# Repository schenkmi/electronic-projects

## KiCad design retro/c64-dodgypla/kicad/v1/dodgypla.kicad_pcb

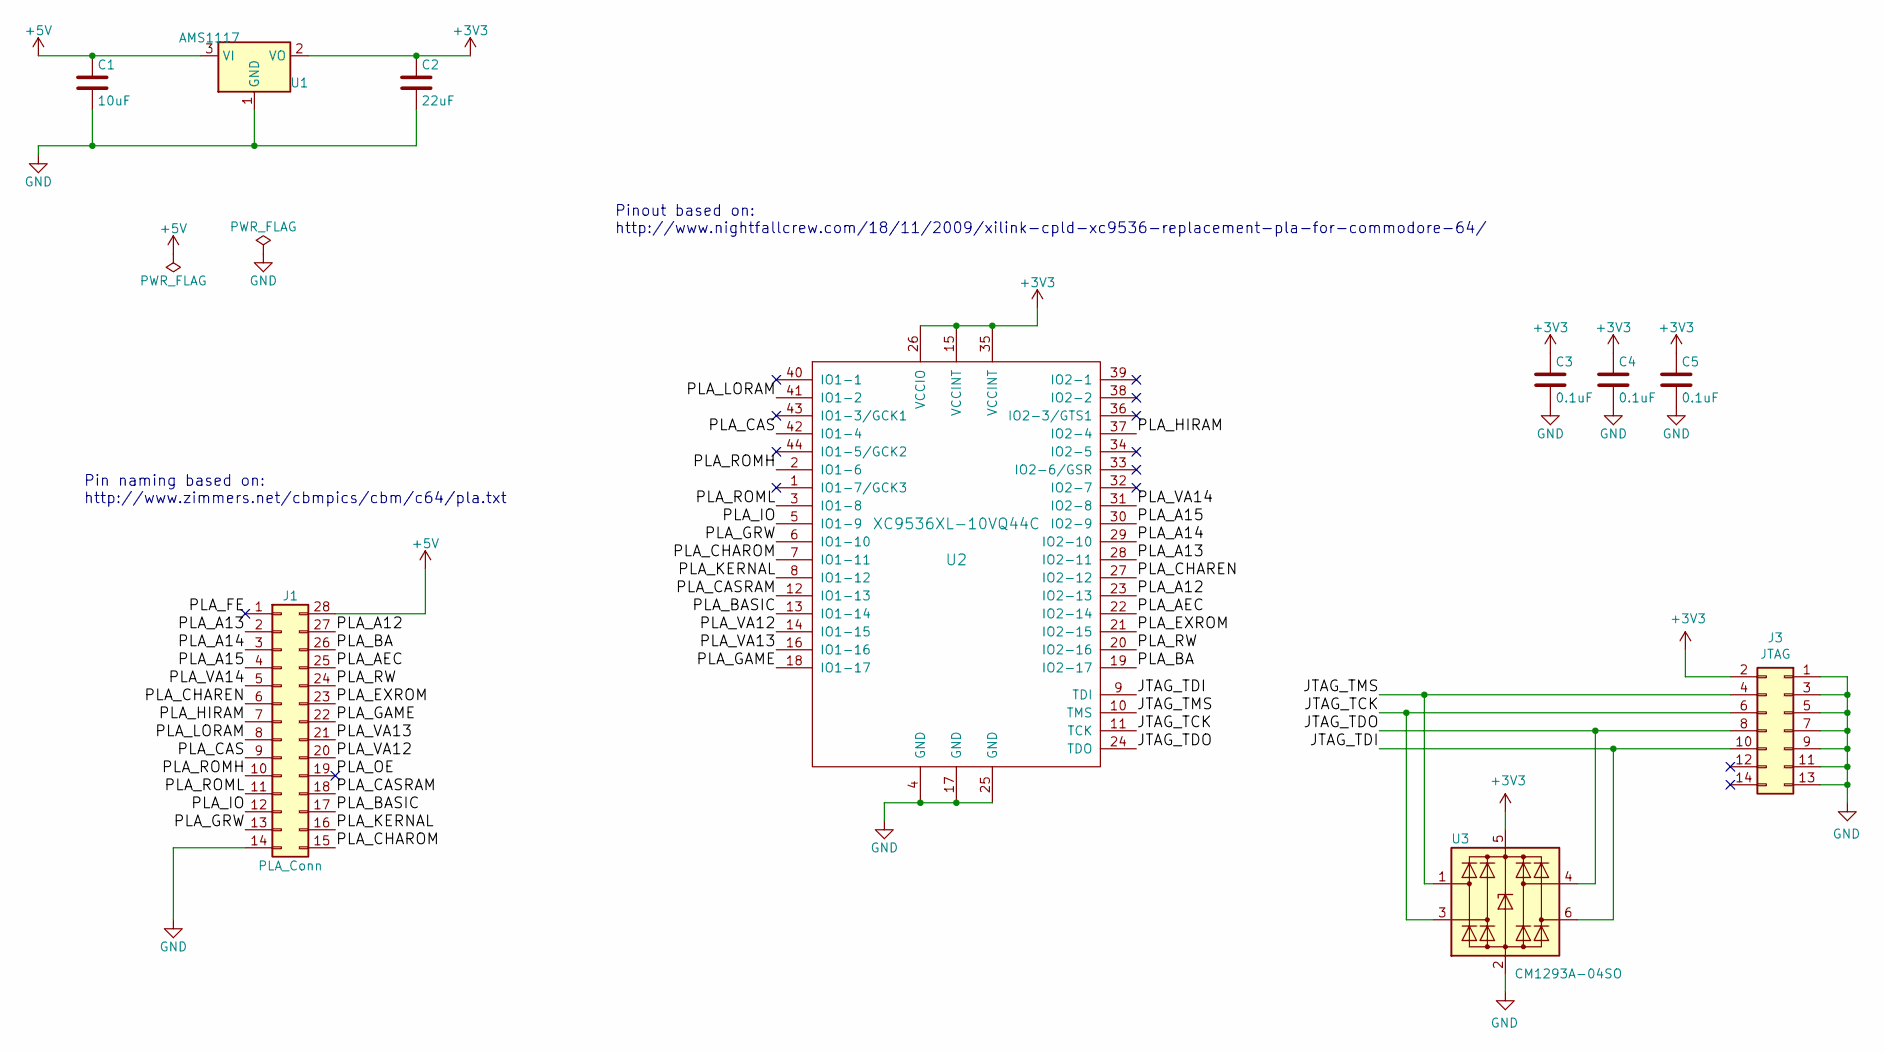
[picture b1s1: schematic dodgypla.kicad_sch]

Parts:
C1: 10uF; C_0805_2012Metric_Pad1.18x1.45mm_HandSolder
C2: 22uF; C_0805_2012Metric_Pad1.18x1.45mm_HandSolder
C3, C4, C5: 0.1uF; C_0805_2012Metric_Pad1.18x1.45mm_HandSolder
J1: PLA_Conn; DIP-28_W15.24mm_Socket
J3: JTAG; PinHeader_2x07_P2.00mm_Vertical
U1: AMS1117; SOT-223-3_TabPin2
U2: XC9536XL-10VQ44C; LQFP-44_10x10mm_P0.8mm
U3: CM1293A−04SO; SC-74-6_1.55x2.9mm_P0.95mm

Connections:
+3V3: C2.1, C3.1, C4.1, C5.1, J3.2, U1.2 (VO), U2.15 (VCCINT), U2.26 (VCCIO), U2.35 (VCCINT), U3.5 (VBUS)
+5V: C1.1, J1.28, U1.3 (VI)
/JTAG_TCK: J3.6, U2.11 (TCK), U3.3 (I/O2)
/JTAG_TDI: J3.10, U2.9 (TDI), U3.6 (I/O4)
/JTAG_TDO: J3.8, U2.24 (TDO), U3.4 (I/O3)
/JTAG_TMS: J3.4, U2.10 (TMS), U3.1 (I/O1)
/PLA_A12: J1.27, U2.23 (IO2-13)
/PLA_A13: J1.2, U2.28 (IO2-11)
/PLA_A14: J1.3, U2.29 (IO2-10)
/PLA_A15: J1.4, U2.30 (IO2-9)
/PLA_AEC: J1.25, U2.22 (IO2-14)
/PLA_BA: J1.26, U2.19 (IO2-17)
/PLA_BASIC: J1.17, U2.13 (IO1-14)
/PLA_CAS: J1.9, U2.42 (IO1-4)
/PLA_CASRAM: J1.18, U2.12 (IO1-13)
/PLA_CHAREN: J1.6, U2.27 (IO2-12)
/PLA_CHAROM: J1.15, U2.7 (IO1-11)
/PLA_EXROM: J1.23, U2.21 (IO2-15)
/PLA_FE: J1.1
/PLA_GAME: J1.22, U2.18 (IO1-17)
/PLA_GRW: J1.13, U2.6 (IO1-10)
/PLA_HIRAM: J1.7, U2.37 (IO2-4)
/PLA_IO: J1.12, U2.5 (IO1-9)
/PLA_KERNAL: J1.16, U2.8 (IO1-12)
/PLA_LORAM: J1.8, U2.41 (IO1-2)
/PLA_OE: J1.19
/PLA_ROMH: J1.10, U2.2 (IO1-6)
/PLA_ROML: J1.11, U2.3 (IO1-8)
/PLA_RW: J1.24, U2.20 (IO2-16)
/PLA_VA12: J1.20, U2.14 (IO1-15)
/PLA_VA13: J1.21, U2.16 (IO1-16)
/PLA_VA14: J1.5, U2.31 (IO2-8)
GND: C1.2, C2.2, C3.2, C4.2, C5.2, J1.14, J3.1, J3.3, J3.5, J3.7, J3.9, J3.11, J3.13, U1.1 (GND), U2.4 (GND), U2.17 (GND), U2.25 (GND), U3.2 (GND)

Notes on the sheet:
Pin naming based on: http://www.zimmers.net/cbmpics/cbm/c64/pla.txt
Pinout based on: http://www.nightfallcrew.com/18/11/2009/xilink-cpld-xc9536-replacement-pla-for-commodore-64/

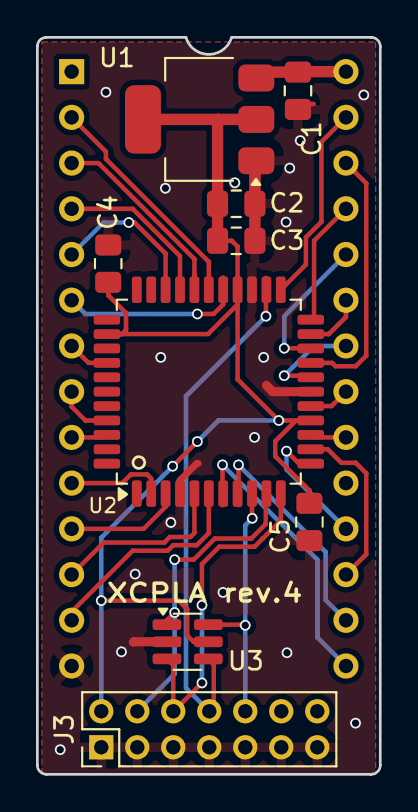
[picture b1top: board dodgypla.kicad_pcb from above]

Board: 2 copper layers, 19.0 x 40.9 mm, 10 parts (0 on the bottom side), 31 nets.

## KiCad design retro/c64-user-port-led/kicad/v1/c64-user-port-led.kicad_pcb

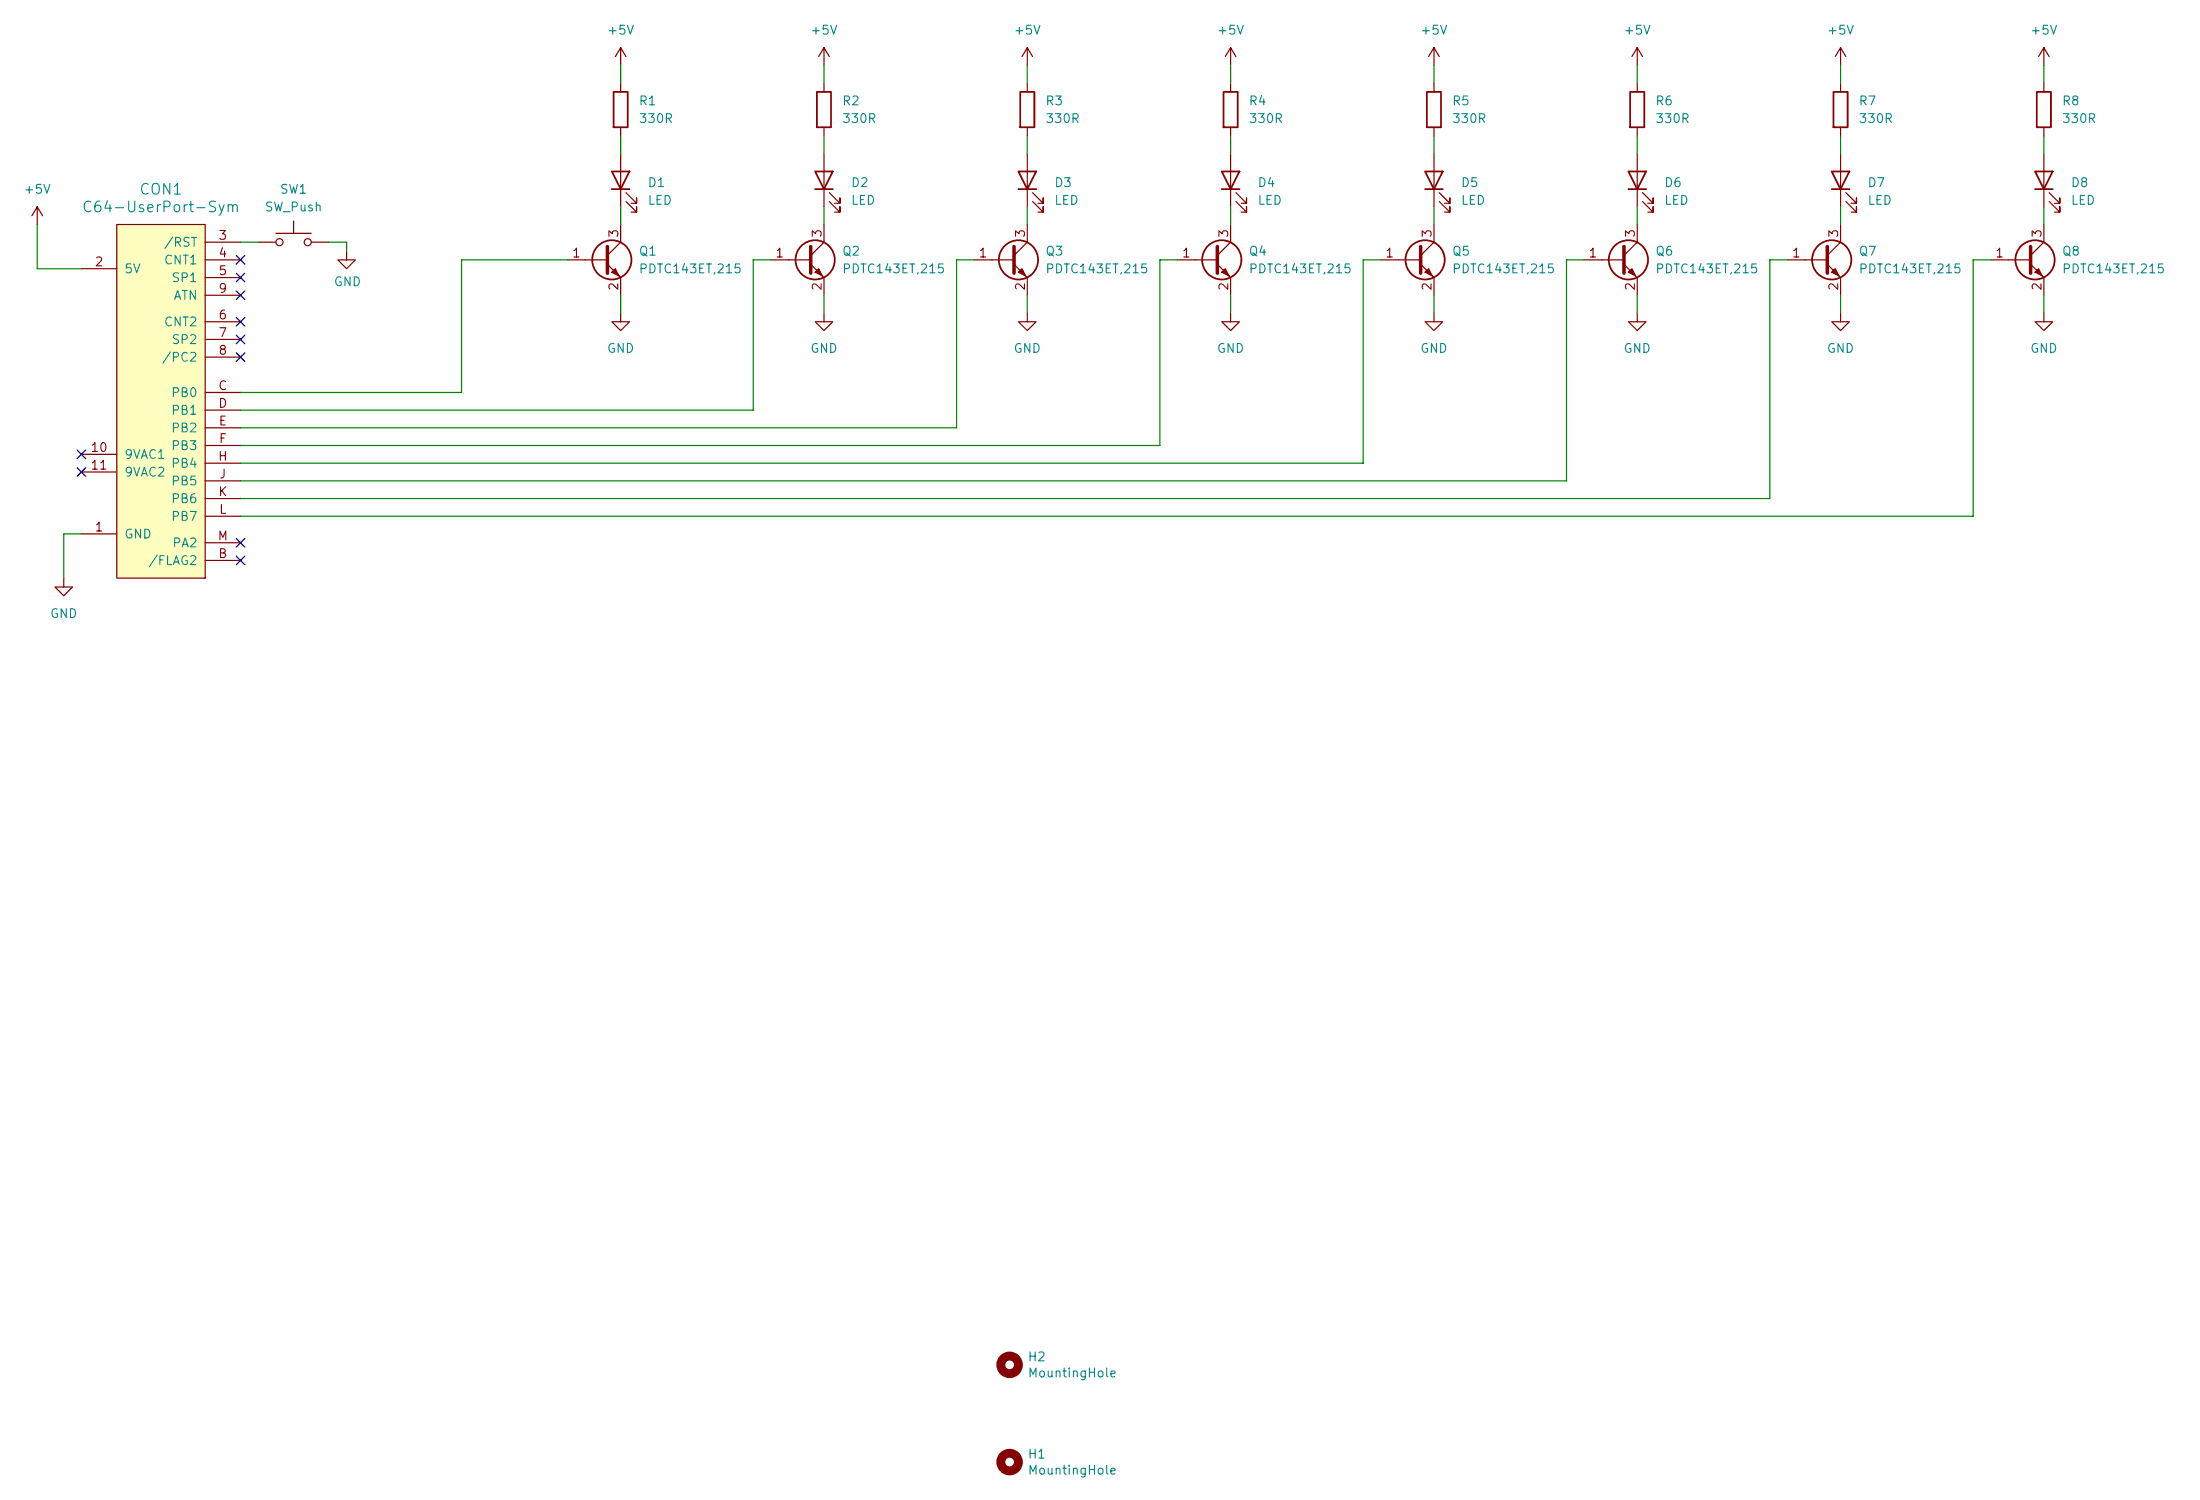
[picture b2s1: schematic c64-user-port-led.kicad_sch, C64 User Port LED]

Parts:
CON1: C64-UserPort-Sym; C64-User-Port-Female_Single-GND
D1, D2, D3, D4, D5, D6, D7, D8: LED; LED_D5.0mm
H1, H2: MountingHole; MountingHole_3.2mm_M3_Pad_Via
Q1, Q2, Q3, Q4, Q5, Q6, Q7, Q8: PDTC143ET,215; SOT-23
R1, R2, R3, R4, R5, R6, R7, R8: 330R; R_0805_2012Metric_Pad1.20x1.40mm_HandSolder
SW1: SW_Push; SW_SPST_CK_RS282G05A3

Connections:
+5V: CON1.2 (5V), R1.1, R2.1, R3.1, R4.1, R5.1, R6.1, R7.1, R8.1
GND: CON1.1 (GND), Q1.2 (E), Q2.2 (E), Q3.2 (E), Q4.2 (E), Q5.2 (E), Q6.2 (E), Q7.2 (E), Q8.2 (E), SW1.2
unnamed: CON1.C (PB0), Q1.1 (B)
unnamed: CON1.D (PB1), Q2.1 (B)
unnamed: CON1.E (PB2), Q3.1 (B)
unnamed: CON1.F (PB3), Q4.1 (B)
unnamed: CON1.H (PB4), Q5.1 (B)
unnamed: CON1.J (PB5), Q6.1 (B)
unnamed: CON1.K (PB6), Q7.1 (B)
unnamed: CON1.L (PB7), Q8.1 (B)
unnamed: CON1.3 (/RST), SW1.1
unnamed: D1.2 (A), R1.2
unnamed: D1.1 (K), Q1.3 (C)
unnamed: D2.2 (A), R2.2
unnamed: D2.1 (K), Q2.3 (C)
unnamed: D3.2 (A), R3.2
unnamed: D3.1 (K), Q3.3 (C)
unnamed: D4.2 (A), R4.2
unnamed: D4.1 (K), Q4.3 (C)
unnamed: D5.2 (A), R5.2
unnamed: D5.1 (K), Q5.3 (C)
unnamed: D6.2 (A), R6.2
unnamed: D6.1 (K), Q6.3 (C)
unnamed: D7.2 (A), R7.2
unnamed: D7.1 (K), Q7.3 (C)
unnamed: D8.2 (A), R8.2
unnamed: D8.1 (K), Q8.3 (C)

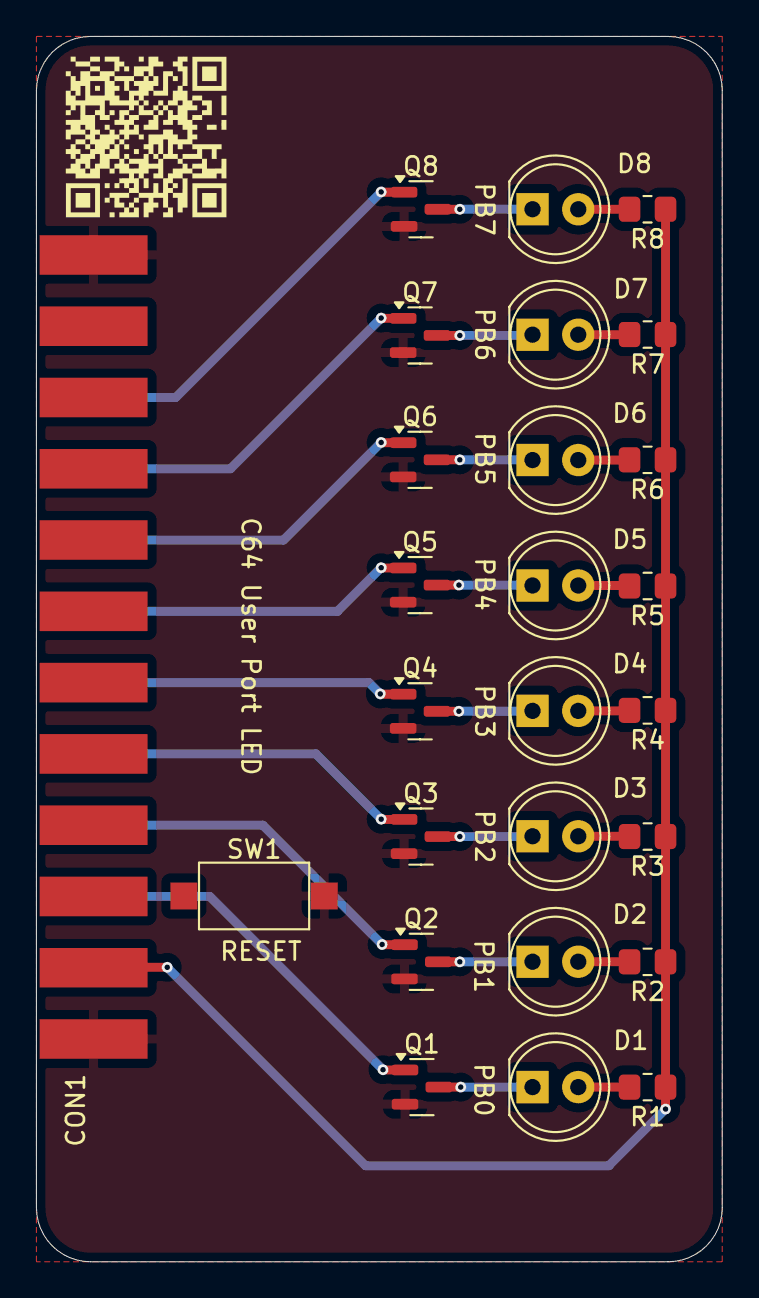
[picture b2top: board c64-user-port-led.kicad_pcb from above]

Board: 2 copper layers, 38.1 x 68.1 mm, 26 parts (0 on the bottom side), 27 nets.

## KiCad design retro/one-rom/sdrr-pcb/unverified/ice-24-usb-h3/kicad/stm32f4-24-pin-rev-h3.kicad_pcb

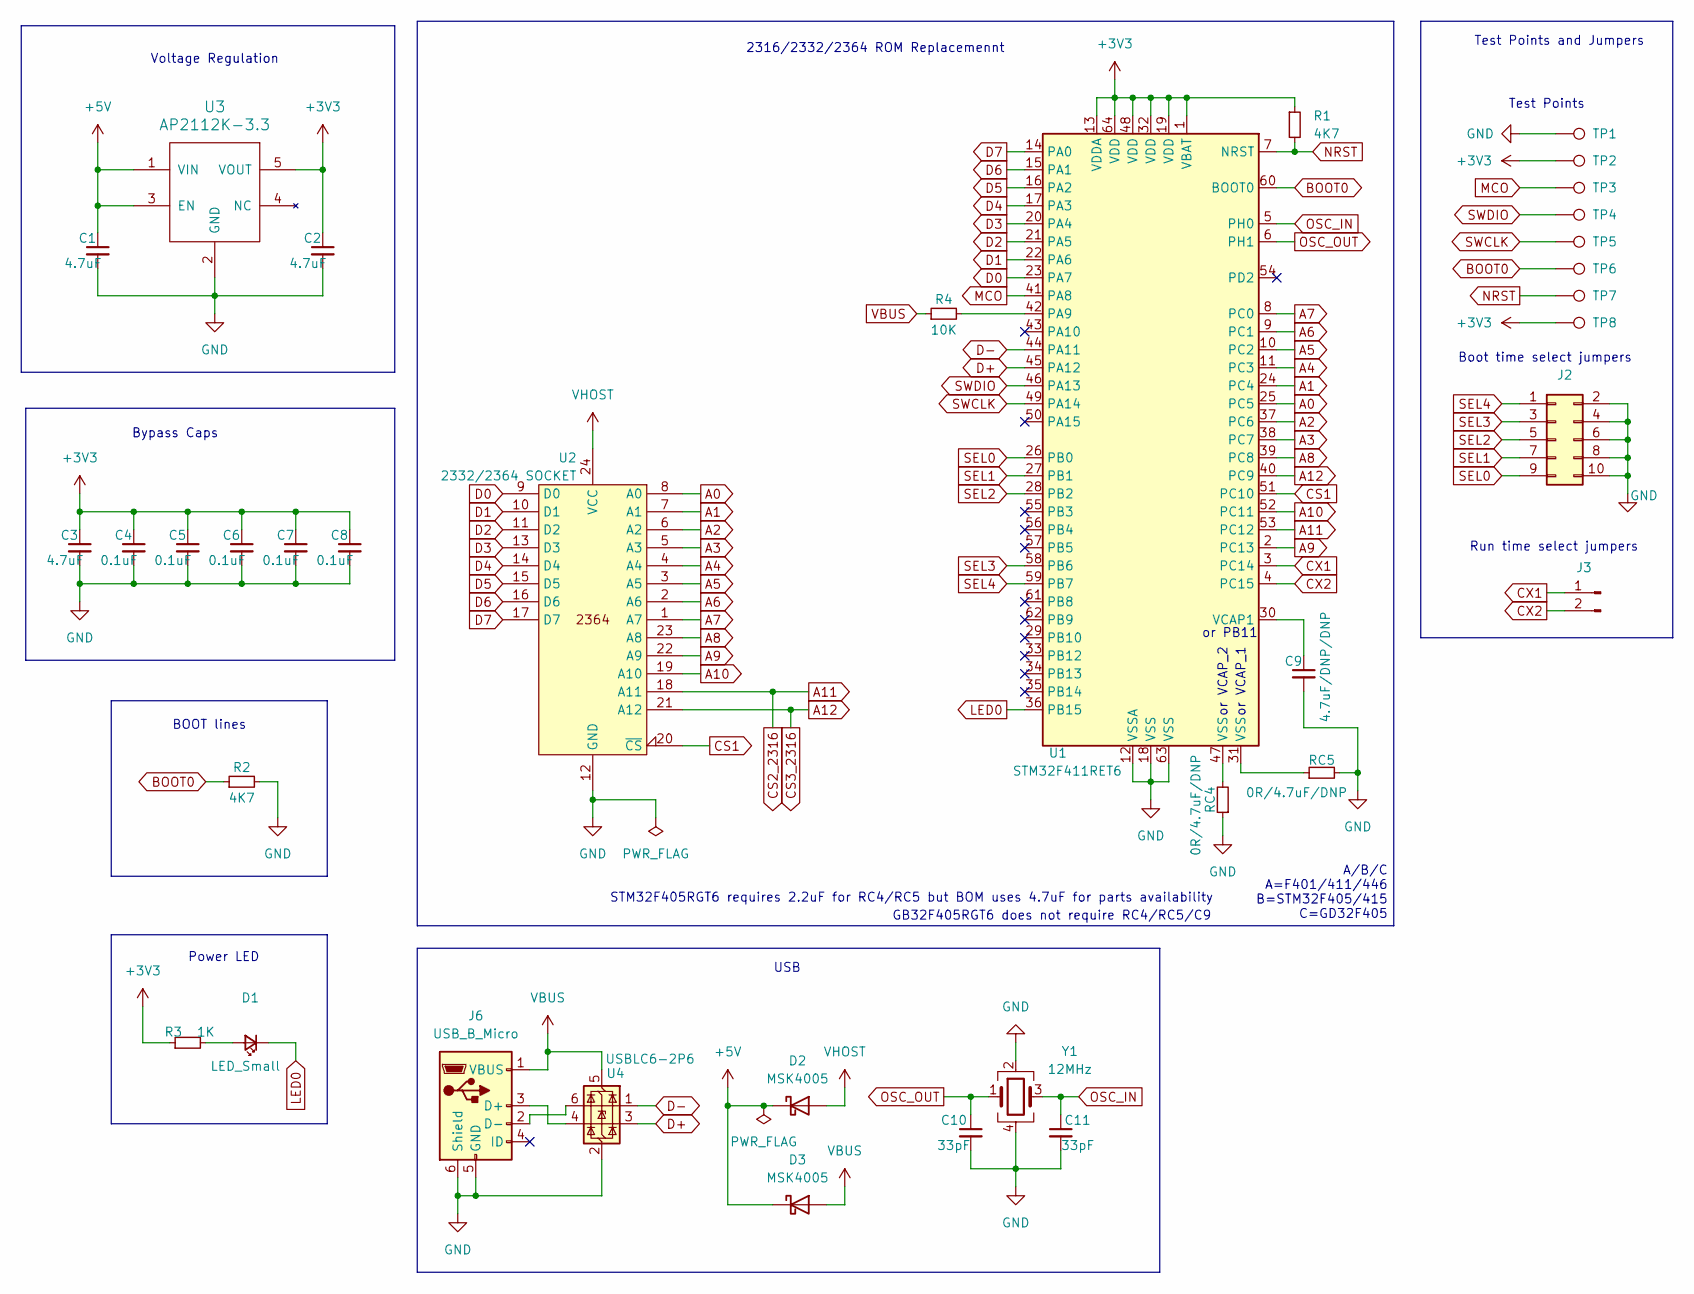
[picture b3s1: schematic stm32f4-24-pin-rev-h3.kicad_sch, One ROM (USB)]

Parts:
C1, C2, C3: 4.7uF; C_0402_1005Metric; LCSC C23733
C4, C5, C6, C7, C8: 0.1uF; C_0402_1005Metric; LCSC C1525
C9: 4.7uF/DNP/DNP; C_0402_1005Metric; LCSC C23733
C10, C11: 33pF; C_0402_1005Metric; LCSC C1562
D1: LED_Small; LED_0603_1608Metric; LCSC C2286
D2, D3: MSK4005; D_SOD-523; LCSC C345957
J2: Conn_02x05_Odd_Even; PinHeader_2x05_P2.54mm_Vertical custom silkscreen
J3: Conn_01x02_Pin; PinHeader_1x02_P2.54mm_Vertical
J6: USB_B_Micro; USB_Micro-B_micro_xnj_073_C404969; LCSC C404969
R1, R2: 4K7; R_0402_1005Metric; LCSC C25900
R3: 1K; R_0402_1005Metric; LCSC C11702
R4: 10K; R_0402_1005Metric; LCSC C25744
RC4, RC5: 0R/4.7uF/DNP; C_0402_1005Metric; LCSC C17168
TP1, TP2, TP3, TP4, TP5, TP7: TestPoint; 1mm smd test point small ss
TP6, TP8: TestPoint; 1mm hole test point small no ss
U1: STM32F411RET6; LQFP-64_10x10mm_P0.5mm; LCSC C94355
U2: 2332/2364 SOCKET; 2x12 dip pin output 600mil centres no ss
U3: AP2112K-3.3; SOT-23-5; LCSC C51118
U4: USBLC6-2P6; SOT-666; LCSC C15999
Y1: 12MHz; Crystal_SMD_3225-4Pin_3.2x2.5mm; LCSC C9002

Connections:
+3V3: C2.1, C3.1, C4.1, C5.1, C6.1, C7.1, C8.1, R1.1, R3.1, TP2.1, TP8.1, U1.1 (VBAT), U1.13 (VDDA), U1.19 (VDD), U1.32 (VDD), U1.48 (VDD), U1.64 (VDD), U3.5 (VOUT)
+5V: C1.1, D2.1 (K), D3.1 (K), U3.1 (VIN), U3.3 (EN)
A0: U1.25 (PC5), U2.8 (A0)
A1: U1.24 (PC4), U2.7 (A1)
A2: U1.37 (PC6), U2.6 (A2)
A3: U1.38 (PC7), U2.5 (A3)
A4: U1.11 (PC3), U2.4 (A4)
A5: U1.10 (PC2), U2.3 (A5)
A6: U1.9 (PC1), U2.2 (A6)
A7: U1.8 (PC0), U2.1 (A7)
A8: U1.39 (PC8), U2.23 (A8)
A9: U1.2 (PC13), U2.22 (A9)
A10: U1.52 (PC11), U2.19 (A10)
A11: U1.53 (PC12), U2.18 (A11)
A12: U1.40 (PC9), U2.21 (A12)
BOOT0: R2.1, TP6.1, U1.60 (BOOT0)
CS1: U1.51 (PC10), U2.20 (~CS)
CX1: J3.1, U1.3 (PC14)
CX2: J3.2, U1.4 (PC15)
D0: U1.23 (PA7), U2.9 (D0)
D1: U1.22 (PA6), U2.10 (D1)
D2: U1.21 (PA5), U2.11 (D2)
D3: U1.20 (PA4), U2.13 (D3)
D4: U1.17 (PA3), U2.14 (D4)
D5: U1.16 (PA2), U2.15 (D5)
D6: U1.15 (PA1), U2.16 (D6)
D7: U1.14 (PA0), U2.17 (D7)
D+: U1.45 (PA12), U4.3 (I/O2)
D-: U1.44 (PA11), U4.1 (I/O1)
GND: C1.2, C2.2, C3.2, C4.2, C5.2, C6.2, C7.2, C8.2, C9.2, C10.2, C11.2, J2.2, J2.4, J2.6, J2.8, J2.10, J6.5 (GND), J6.6 (Shield), R2.2, RC4.1, RC5.2, TP1.1, U1.12 (VSSA), U1.18 (VSS), U1.63 (VSS), U2.12 (GND), U3.2 (GND), U4.2 (GND), Y1.2, Y1.4
LED0: D1.1 (K), U1.36 (PB15)
MCO: TP3.1, U1.41 (PA8)
NRST: R1.2, TP7.1, U1.7 (NRST)
unnamed: D1.2 (A), R3.2
unnamed: J6.3 (D+), U4.4 (I/O2)
unnamed: J6.2 (D-), U4.6 (I/O1)
unnamed: RC4.2, U1.47 (VSS)
unnamed: RC5.1, U1.31 (VSS)
unnamed: R4.2, U1.42 (PA9)
unnamed: C9.1, U1.30 (VCAP1)
OSC_IN: C11.1, U1.5 (PH0), Y1.3
OSC_OUT: C10.1, U1.6 (PH1), Y1.1
SEL0: J2.9, U1.26 (PB0)
SEL1: J2.7, U1.27 (PB1)
SEL2: J2.5, U1.28 (PB2)
SEL3: J2.3, U1.58 (PB6)
SEL4: J2.1, U1.59 (PB7)
SWCLK: TP5.1, U1.49 (PA14)
SWDIO: TP4.1, U1.46 (PA13)
VBUS: D3.2 (A), J6.1 (VBUS), R4.1, U4.5 (VBUS)
VHOST: D2.2 (A), U2.24 (VCC)

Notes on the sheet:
or VCAP_1
or VCAP_2
Run time select jumpers
USB
BOOT lines
Voltage Regulation
2316/2332/2364 ROM Replacemennt
Power LED
or PB11
GB32F405RGT6 does not require RC4/RC5/C9
Test Points
Bypass Caps
Boot time select jumpers
A/B/C A=F401/411/446 B=STM32F405/415 C=GD32F405
Test Points and Jumpers
STM32F405RGT6 requires 2.2uF for RC4/RC5 but BOM uses 4.7uF for parts availability

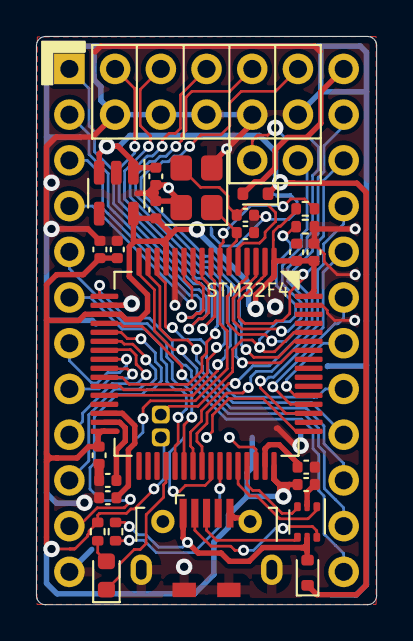
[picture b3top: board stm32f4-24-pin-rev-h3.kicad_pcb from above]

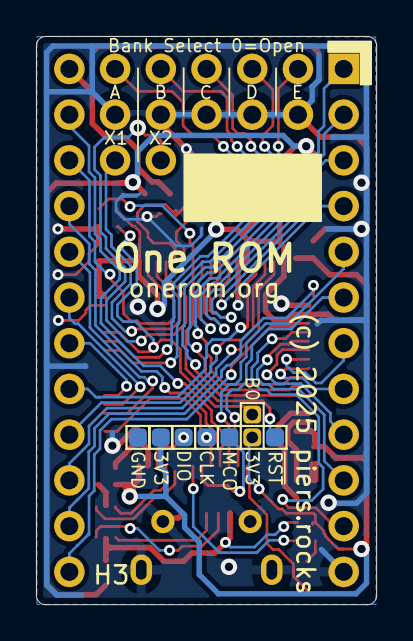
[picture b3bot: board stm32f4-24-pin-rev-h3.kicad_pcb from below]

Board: 2 copper layers, 18.9 x 31.6 mm, 36 parts (8 on the bottom side), 51 nets.

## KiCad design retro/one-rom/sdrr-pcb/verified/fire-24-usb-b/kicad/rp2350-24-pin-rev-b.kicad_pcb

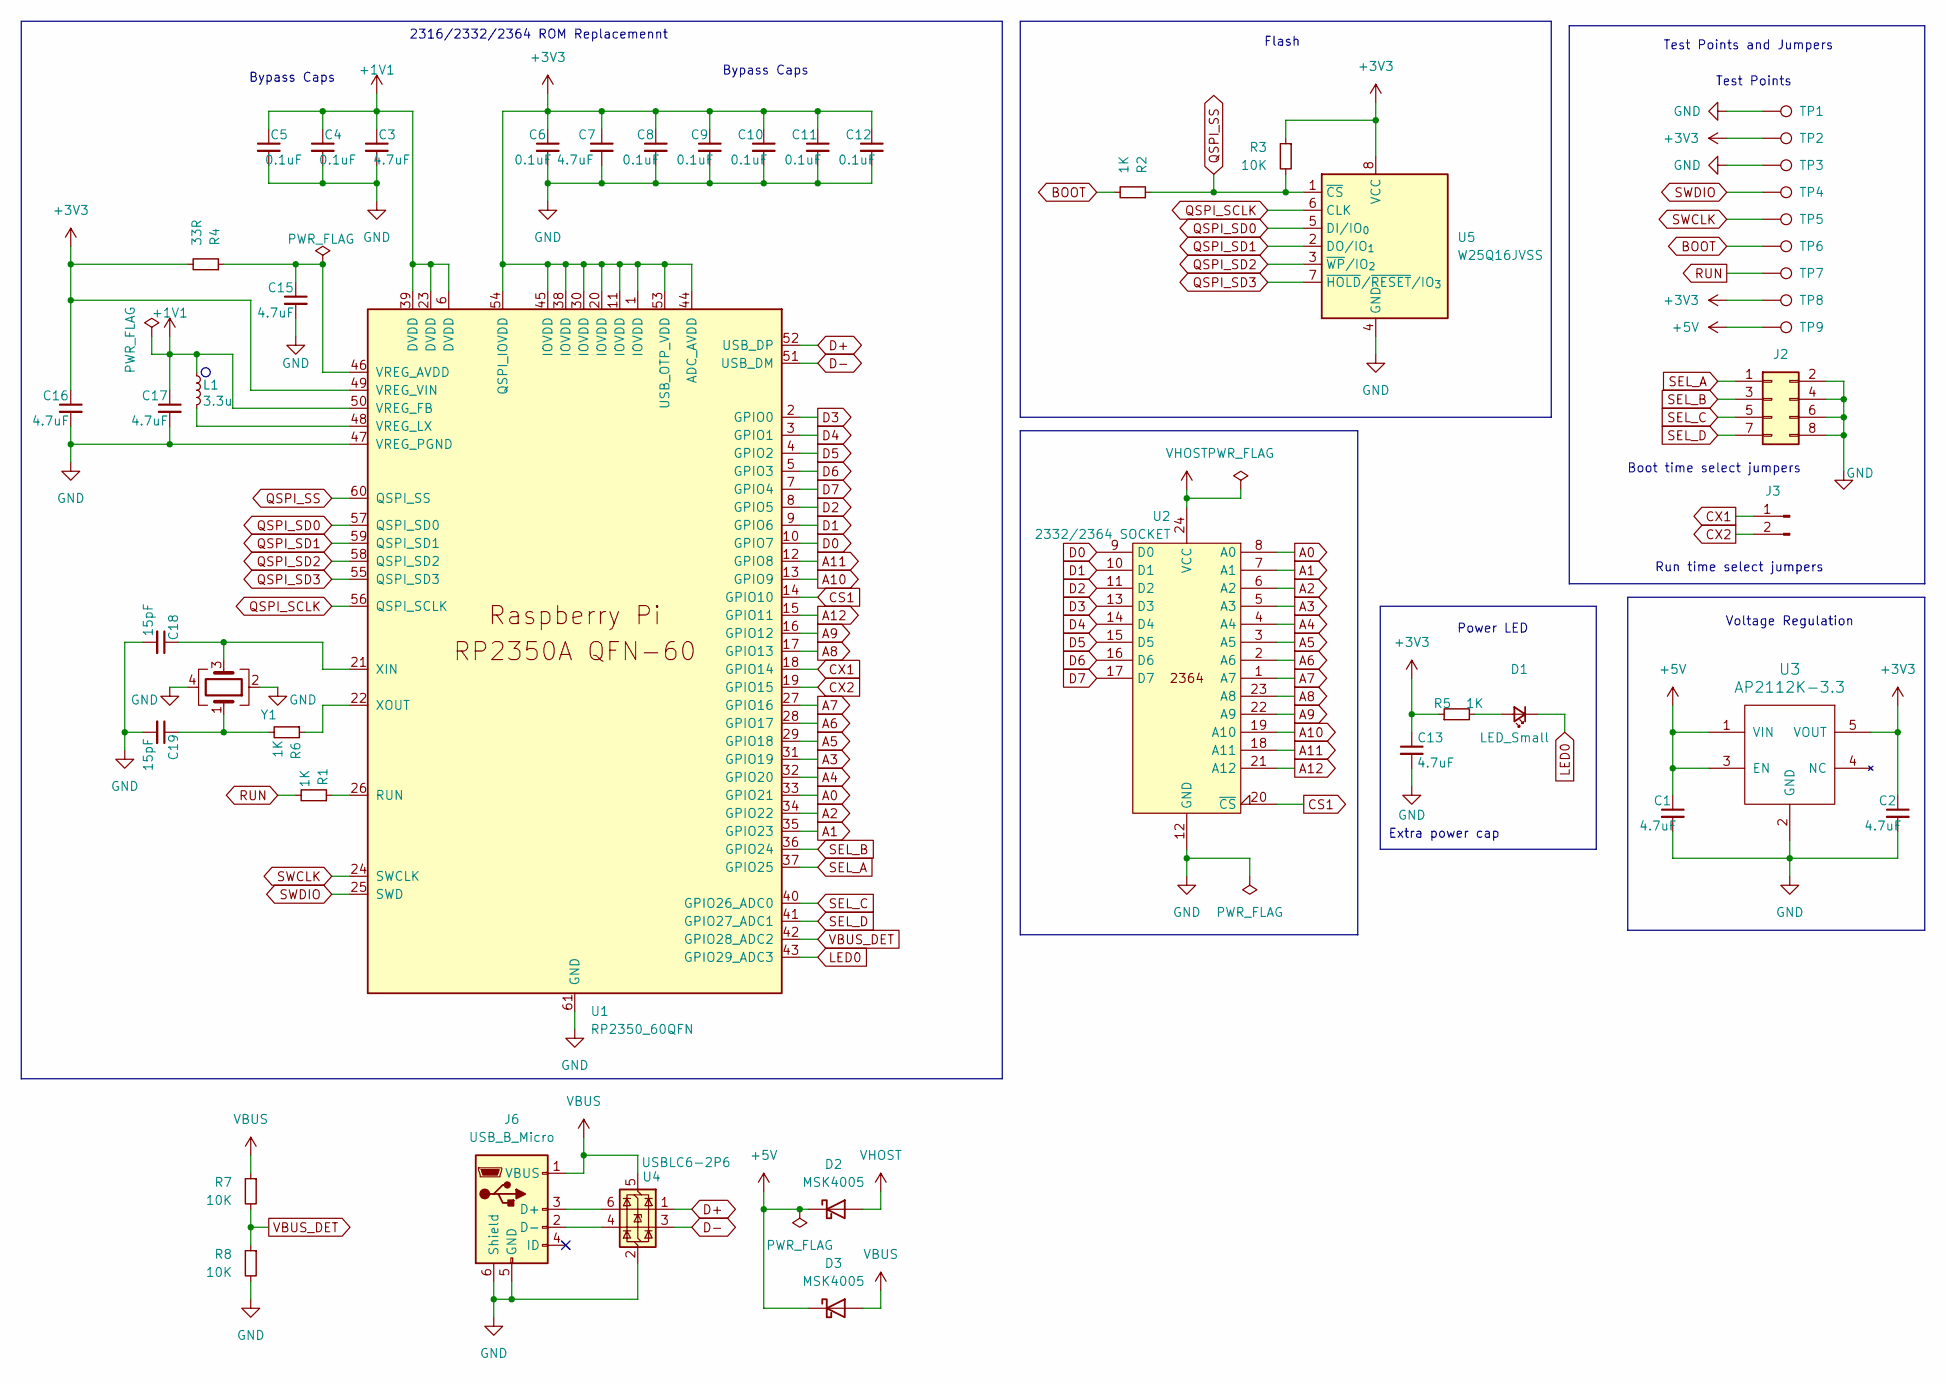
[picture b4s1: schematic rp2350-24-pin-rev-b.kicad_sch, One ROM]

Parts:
C1, C2, C3, C7, C13, C15: 4.7uF; C_0402_1005Metric; LCSC C23733
C4, C5, C6, C8, C9, C10, C11, C12: 0.1uF; C_0402_1005Metric; LCSC C1525
C16, C17: 4.7uF; C_0402_1005Metric_small_pads; LCSC C23733
C18, C19: 15pF; C_0402_1005Metric; LCSC C1548
D1: LED_Small; LED_0603_1608Metric; LCSC C2286
D2, D3: MSK4005; D_SOD-523; LCSC C345957
J2: Conn_02x04_Odd_Even; PinHeader_2x04_P2.54mm_Vertical custom silkscreen
J3: Conn_01x02_Pin; PinHeader_1x02_P2.54mm_Vertical
J6: USB_B_Micro; USB_Micro-B_micro_xnj_073_C404969; LCSC C404969
L1: 3.3u; L_pol_2016; LCSC C42411119
R1, R2, R5, R6: 1K; R_0402_1005Metric; LCSC C11702
R3, R7, R8: 10K; R_0402_1005Metric; LCSC C25744
R4: 33R; R_0402_1005Metric; LCSC C25105
TP1, TP2, TP3, TP4, TP5, TP6, TP7, TP8, TP9: TestPoint; 1mm smd test point small ss
U1: RP2350_60QFN; RP2350-QFN-60-1EP_7x7_P0.4mm_EP3.4x3.4mm_ThermalVias; LCSC C42411118
U2: 2332/2364 SOCKET; 2x12 dip pin output 600mil centres no ss
U3: AP2112K-3.3; SOT-23-5; LCSC C51118
U4: USBLC6-2P6; SOT-666; LCSC C15999
U5: W25Q16JVSS; Winbond_USON-8-1EP_3x2mm_P0.5mm_EP0.2x1.6mm; LCSC C2843335
Y1: Crystal_GND24; Crystal_SMD_Abracon_ABM8G-4Pin_3.2x2.5mm; LCSC C20625731

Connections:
+1V1: C3.1, C4.1, C5.1, C17.1, L1.1, U1.6 (DVDD), U1.23 (DVDD), U1.39 (DVDD), U1.50 (VREG_FB)
+3V3: C2.1, C6.1, C7.1, C8.1, C9.1, C10.1, C11.1, C12.1, C13.1, C16.1, R3.1, R4.2, R5.1, TP2.1, TP8.1, U1.1 (IOVDD), U1.11 (IOVDD), U1.20 (IOVDD), U1.30 (IOVDD), U1.38 (IOVDD), U1.44 (ADC_AVDD), U1.45 (IOVDD), U1.49 (VREG_VIN), U1.53 (USB_OTP_VDD), U1.54 (QSPI_IOVDD), U3.5 (VOUT), U5.8 (VCC)
+5V: C1.1, D2.1 (K), D3.1 (K), TP9.1, U3.1 (VIN), U3.3 (EN)
A0: U1.33 (GPIO21), U2.8 (A0)
A1: U1.35 (GPIO23), U2.7 (A1)
A2: U1.34 (GPIO22), U2.6 (A2)
A3: U1.31 (GPIO19), U2.5 (A3)
A4: U1.32 (GPIO20), U2.4 (A4)
A5: U1.29 (GPIO18), U2.3 (A5)
A6: U1.28 (GPIO17), U2.2 (A6)
A7: U1.27 (GPIO16), U2.1 (A7)
A8: U1.17 (GPIO13), U2.23 (A8)
A9: U1.16 (GPIO12), U2.22 (A9)
A10: U1.13 (GPIO9), U2.19 (A10)
A11: U1.12 (GPIO8), U2.18 (A11)
A12: U1.15 (GPIO11), U2.21 (A12)
BOOT: R2.2, TP6.1
CS1: U1.14 (GPIO10), U2.20 (~CS)
CX1: J3.1, U1.18 (GPIO14)
CX2: J3.2, U1.19 (GPIO15)
D0: U1.10 (GPIO7), U2.9 (D0)
D1: U1.9 (GPIO6), U2.10 (D1)
D2: U1.8 (GPIO5), U2.11 (D2)
D3: U1.2 (GPIO0), U2.13 (D3)
D4: U1.3 (GPIO1), U2.14 (D4)
D5: U1.4 (GPIO2), U2.15 (D5)
D6: U1.5 (GPIO3), U2.16 (D6)
D7: U1.7 (GPIO4), U2.17 (D7)
D+: U1.52 (USB_DP), U4.1 (I/O1)
D-: U1.51 (USB_DM), U4.3 (I/O2)
GND: C1.2, C2.2, C3.2, C4.2, C5.2, C6.2, C7.2, C8.2, C9.2, C10.2, C11.2, C12.2, C13.2, C15.2, C16.2, C17.2, C18.2, C19.2, J2.2, J2.4, J2.6, J2.8, J6.5 (GND), J6.6 (Shield), R8.2, TP1.1, TP3.1, U1.47 (VREG_PGND), U1.61 (GND), U2.12 (GND), U3.2 (GND), U4.2 (GND), U5.4 (GND), Y1.2, Y1.4
LED0: D1.1 (K), U1.43 (GPIO29_ADC3)
unnamed: C19.1, R6.2, Y1.1
unnamed: D1.2 (A), R5.2
unnamed: J6.3 (D+), U4.6 (I/O1)
unnamed: J6.2 (D-), U4.4 (I/O2)
unnamed: R1.1, U1.26 (RUN)
unnamed: C15.1, R4.1, U1.46 (VREG_AVDD)
unnamed: L1.2, U1.48 (VREG_LX)
unnamed: C18.1, U1.21 (XIN), Y1.3
unnamed: R6.1, U1.22 (XOUT)
QSPI_SCLK: U1.56 (QSPI_SCLK), U5.6 (CLK)
QSPI_SD0: U1.57 (QSPI_SD0), U5.5 (DI/IO_{0})
QSPI_SD1: U1.59 (QSPI_SD1), U5.2 (DO/IO_{1})
QSPI_SD2: U1.58 (QSPI_SD2), U5.3 (~WP/IO_{2})
QSPI_SD3: U1.55 (QSPI_SD3), U5.7 (~HOLD/~RESET/IO_{3})
QSPI_SS: R2.1, R3.2, U1.60 (QSPI_SS), U5.1 (~CS)
RUN: R1.2, TP7.1
SEL_A: J2.1, U1.37 (GPIO25)
SEL_B: J2.3, U1.36 (GPIO24)
SEL_C: J2.5, U1.40 (GPIO26_ADC0)
SEL_D: J2.7, U1.41 (GPIO27_ADC1)
SWCLK: TP5.1, U1.24 (SWCLK)
SWDIO: TP4.1, U1.25 (SWD)
VBUS: D3.2 (A), J6.1 (VBUS), R7.1, U4.5 (VBUS)
VBUS_DET: R7.2, R8.1, U1.42 (GPIO28_ADC2)
VHOST: D2.2 (A), U2.24 (VCC)

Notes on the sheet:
Run time select jumpers
Test Points
Voltage Regulation
Extra power cap
2316/2332/2364 ROM Replacemennt
Bypass Caps
Power LED
Flash
Boot time select jumpers
Test Points and Jumpers

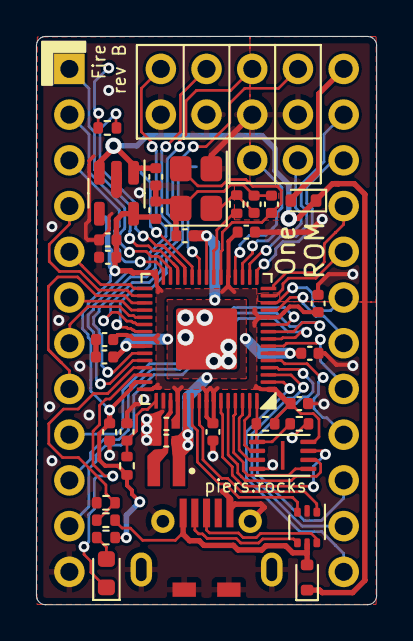
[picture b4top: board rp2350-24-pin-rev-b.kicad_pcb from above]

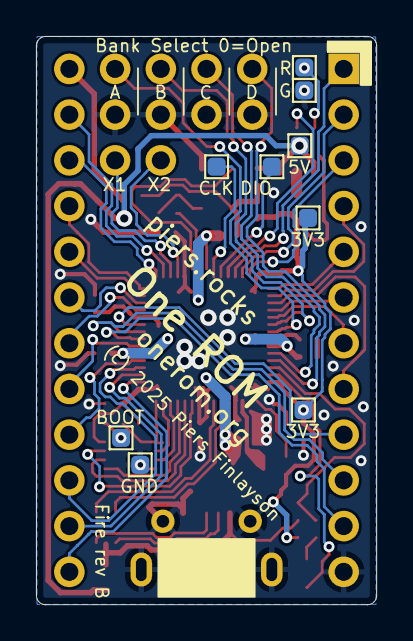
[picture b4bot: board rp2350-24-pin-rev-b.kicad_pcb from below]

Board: 2 copper layers, 18.9 x 31.6 mm, 48 parts (9 on the bottom side), 57 nets.

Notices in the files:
retro/one-rom/sdrr-pcb/unverified/ice-24-usb-h3/kicad/stm32f4-24-pin-rev-h3.kicad_pcb:
(c) 2025 piers.rocks
retro/one-rom/sdrr-pcb/verified/fire-24-usb-b/kicad/rp2350-24-pin-rev-b.kicad_pcb:
(c) 2025 Piers Finlayson
retro/one-rom/sdrr-pcb/verified/rp2350-24-pin-rev-a/kicad/rp2350-24-pin-rev-a.kicad_pcb:
(c) 2025
